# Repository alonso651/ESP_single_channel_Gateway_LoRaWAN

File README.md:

Gateway LoRaWAN ESP8266 de un solo canal
========================================
Febrero de 2019 

Single Channel Gateway LoRaWAN
------------------------------
Es un Gateway LoRaWAN de un único canal.

Cuenta con dos modos de funcionamiento:
1. Normal: Un solo canal (0-7) y un SF (SF7-SF12).
2. CAD: Un solo canal (0-7) y todos los SF de SF7 a SF12 (Más versátil).

En la configuración actual se utilizó la primer sub banda (sub banda 1) de la banda 
de frecuencias ISM US915 MHz. 

Sub banda 1 (903.9 - 905.3 MHz): 

	· Canal 0 - 903.9 MHz
	· Canal 1 - 904.1 MHz
	· Canal 2 - 904.3 MHz
	· Canal 3 - 904.5 MHz
	· Canal 4 - 904.7 MHz
	· Canal 5 - 904.9 MHz
	· Canal 6 - 905.1 MHz
	· Canal 7 - 905.3 MHz

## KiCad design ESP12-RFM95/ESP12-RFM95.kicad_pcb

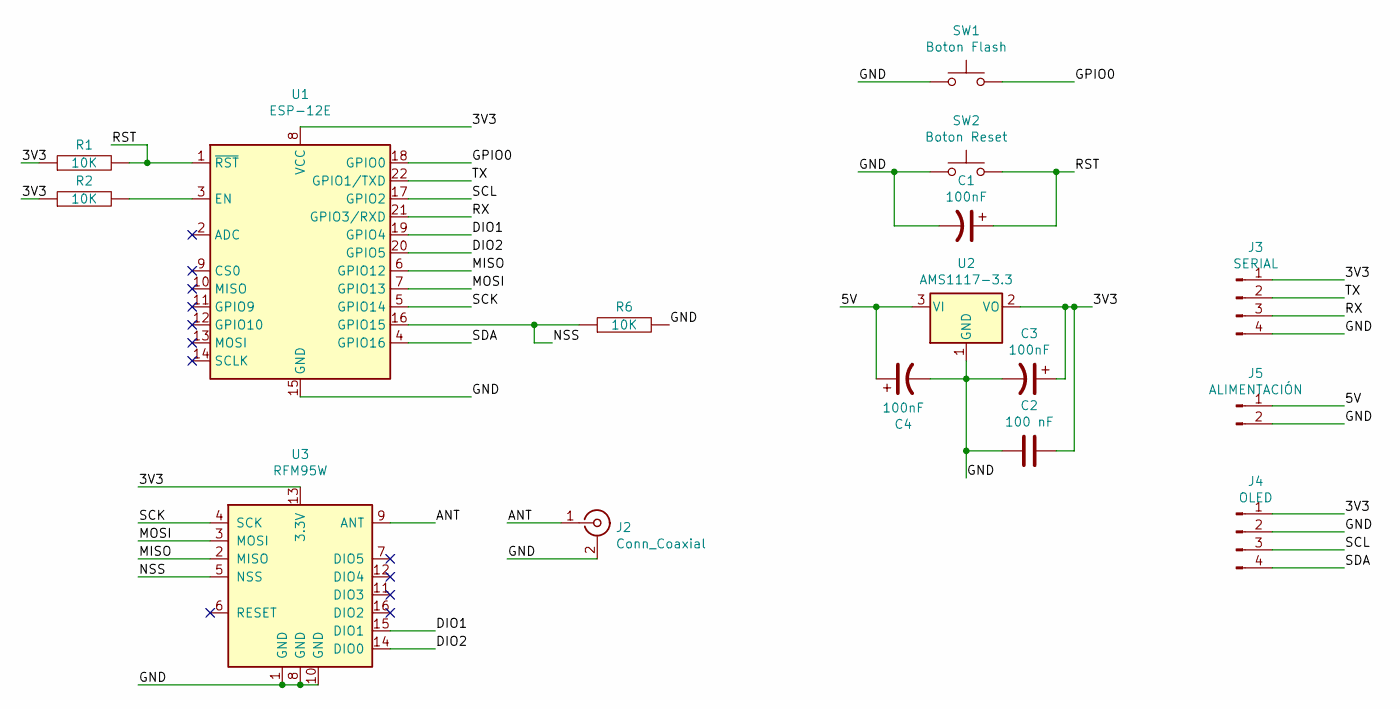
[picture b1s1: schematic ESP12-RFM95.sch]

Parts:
C1, C3, C4: 100nF; CP_Radial_D5.0mm_P2.50mm
C2: 100 nF; C_Disc_D3.0mm_W2.0mm_P2.50mm
J2: Conn_Coaxial; SMA_Amphenol_901-144_Vertical
J3: SERIAL; PinHeader_1x04_P2.54mm_Horizontal
J4: OLED; I2C_SSD1306
J5: ALIMENTACIÓN; PinHeader_1x02_P2.54mm_Vertical
R1, R2, R6: 10K; R_Axial_DIN0207_L6.3mm_D2.5mm_P5.08mm_Vertical
SW1: Boton Flash; SW_DIP_SPSTx01_Slide_6.7x4.1mm_W6.73mm_P2.54mm_LowProfile_J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
SW2: Boton Reset; SW_DIP_SPSTx01_Slide_6.7x4.1mm_W6.73mm_P2.54mm_LowProfile_J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
U1: ESP-12E; ESP-12E_2
U2: AMS1117-3.3; SOT-223-3_TabPin2
U3: RFM95W; HOPERF_RFM9XW_SMD

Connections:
/3V3: C2.1, C3.1, J3.1, J4.1, R1.1, R2.1, U1.8 (VCC), U2.2 (VO), U3.13 (3.3V); also elsewhere on the board
/5V: C4.1, J5.1, U2.3 (VI)
/ANT: J2.1 (In), U3.9 (ANT)
/DIO1: U1.19 (GPIO4), U3.15 (DIO1)
/DIO2: U1.20 (GPIO5), U3.14 (DIO0)
/GND: C1.2, C2.2, C3.2, C4.2, J2.2 (Ext), J3.4, J4.2, J5.2, R6.2, SW1.1, SW2.1, U1.15 (GND), U2.1 (GND), U3.1 (GND), U3.8 (GND), U3.10 (GND); also elsewhere on the board
/GPIO0: SW1.2, U1.18 (GPIO0)
/MISO: U1.6 (GPIO12), U3.2 (MISO)
/MOSI: U1.7 (GPIO13), U3.3 (MOSI)
/NSS: R6.1, U1.16 (GPIO15), U3.5 (NSS)
/RST: C1.1, R1.2, SW2.2, U1.1 (~RST)
/RX: J3.3, U1.21 (GPIO3/RXD)
/SCK: U1.5 (GPIO14), U3.4 (SCK)
/SCL: J4.3, U1.17 (GPIO2); also elsewhere on the board
/SDA: J4.4, U1.4 (GPIO16); also elsewhere on the board
/TX: J3.2, U1.22 (GPIO1/TXD)
unnamed: R2.2, U1.3 (EN)

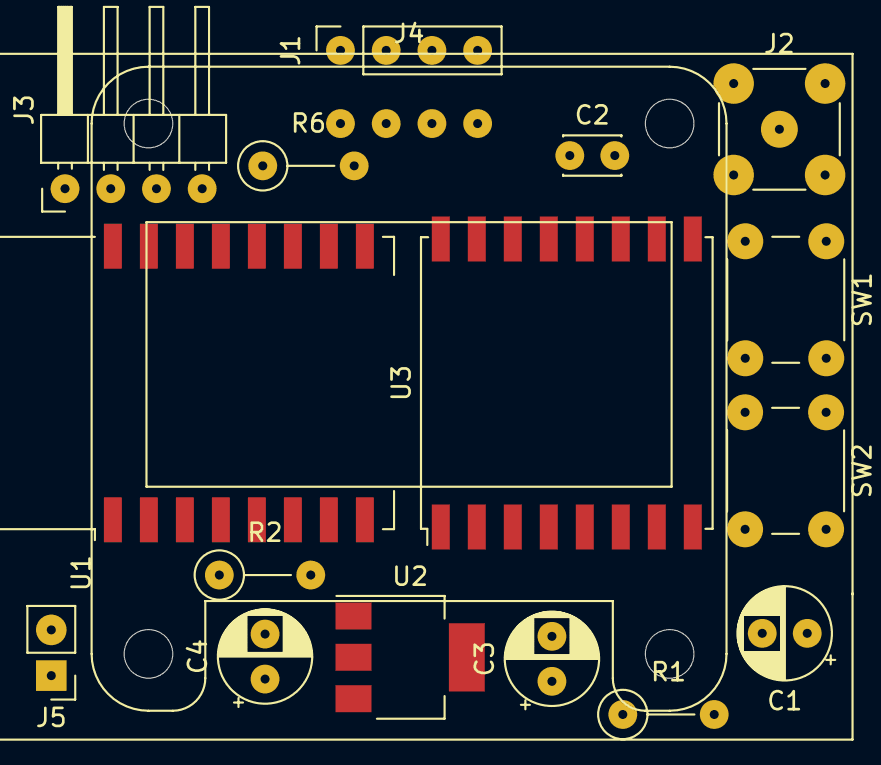
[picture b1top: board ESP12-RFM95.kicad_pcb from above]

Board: 2 copper layers, 17 parts (0 on the bottom side), 17 nets.

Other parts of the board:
J1: I2C; PinSocket_1x04_P2.54mm_Vertical

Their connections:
/3V3: J1.1; also elsewhere on the board
/GND: J1.2; also elsewhere on the board
/SCL: J1.3; also elsewhere on the board
/SDA: J1.4; also elsewhere on the board

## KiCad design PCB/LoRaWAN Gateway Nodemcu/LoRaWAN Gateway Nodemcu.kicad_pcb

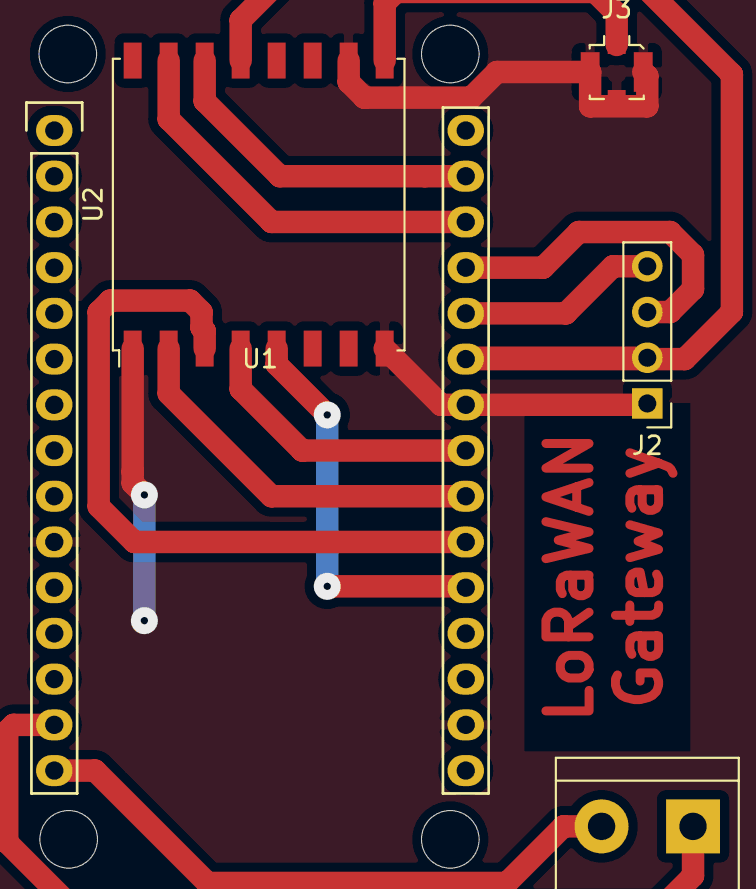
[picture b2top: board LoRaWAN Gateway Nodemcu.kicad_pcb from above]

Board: 2 copper layers, 5 parts (0 on the bottom side), 13 nets.

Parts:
J1: 5V in; TerminalBlock_bornier-2_P5.08mm
J2: Display Oled I2C; PinHeader_1x04_P2.54mm_Vertical
J3: Antena; U.FL_Molex_MCRF_73412-0110_Vertical
U1: NodeMCU Amica R2; NodeMCU_Amica_R2
U2: RFM95W; HOPERF_RFM9XW_SMD

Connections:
/3v3: J2.2, U1.11, U1.16, U1.25, U2.13
/ANT: J3.1, U2.9
/DIO0: U1.29, U2.14
/DIO1: U1.28, U2.15
/GND: J2.1, J3.2, U1.10, U1.17, U1.24, U2.1, U2.8, U2.10
/GNDin: J1.1, U1.14
/MISO: U1.22, U2.2
/MOSI: U1.21, U2.3
/NSS: U1.20, U2.5
/SCK: U1.23, U2.4
/SCL: J2.3, U1.27
/SDA: J2.4, U1.26
/Vin: J1.2, U1.15

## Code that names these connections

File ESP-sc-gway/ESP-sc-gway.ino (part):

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	// Pins are defined and set in loraModem.h
    pinMode(pins.ss, OUTPUT);
	pinMode(pins.rst, OUTPUT);
    pinMode(pins.dio0, INPUT);								// This pin is interrupt
	pinMode(pins.dio1, INPUT);								// This pin is interrupt
	//pinMode(pins.dio2, INPUT);

	// Init the SPI pins
#if ESP32_ARCH==1
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	LoraUp.payLoad[0]= 0;
	LoraUp.payLength = 0;						// Init the length to 0

	// init interrupt handlers, which are shared for GPIO15 / D8, 
	// we switch on HIGH interrupts
	if (pins.dio0 == pins.dio1) {
		//SPI.usingInterrupt(digitalPinToInterrupt(pins.dio0));
		attachInterrupt(pins.dio0, Interrupt_0, RISING);		// Share interrupts
	}
	// Or in the traditional Comresult case
	else {
		//SPI.usingInterrupt(digitalPinToInterrupt(pins.dio0));
		//SPI.usingInterrupt(digitalPinToInterrupt(pins.dio1));
		attachInterrupt(pins.dio0, Interrupt_0, RISING);	// Separate interrupts
		attachInterrupt(pins.dio1, Interrupt_1, RISING);	// Separate interrupts		
	}
	
	writeConfig( CONFIGFILE, &gwayConfig);					// Write config
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
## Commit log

2019-02-14 ESP Single Channel LoRaWAN
    ESP8266 Single Channel Gateway LoRaWAN SF7-SF12 (CAD mode)
2019-02-14 README
    readme
2019-02-14 README
2019-09-29 version 1.1

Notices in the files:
ESP-sc-gway/ESP-sc-gway.ino:
Copyright (c) 2016, 2017, 2018 Maarten Westenberg version for ESP8266
All rights reserved. This program and the accompanying materials
are made available under the terms of the MIT License
